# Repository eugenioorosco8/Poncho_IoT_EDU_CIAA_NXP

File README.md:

# Poncho_IoT_EDU_CIAA_NXP
El proyecto argentino CIAA, con alcance latinoamericano, lleva adelante el desarrollo y producción de sistemas embebidos, con fines educativos, industriales y científicos. El presente es un sistema embebido integral basado en la versión EDU-CIAA NXP, con fines educativos y de investigación aplicada. Se desarrolla el Hardware y el Software requeridos con el fin de proporcionar un circuito impreso de expansión de “Internet de las cosas” (IoT), capaz de brindar múltiples tecnologías como son: Wifi, Bluetooth, GSM, portabilidad SD, y RF. El desarrollo posee dos partes principales. La primera, basada en un microcontrolador ATMEL, consiste en la utilización de nodos provistos de sensores y módulos de comunicación. En la segunda parte, se diseña un nodo central de gran capacidad de procesamiento. La plataforma de desarrollo Nacional EDU-CIAA NXP, en conjunto con la placa de expansión IoT diseñada se emplea en la segunda etapa.

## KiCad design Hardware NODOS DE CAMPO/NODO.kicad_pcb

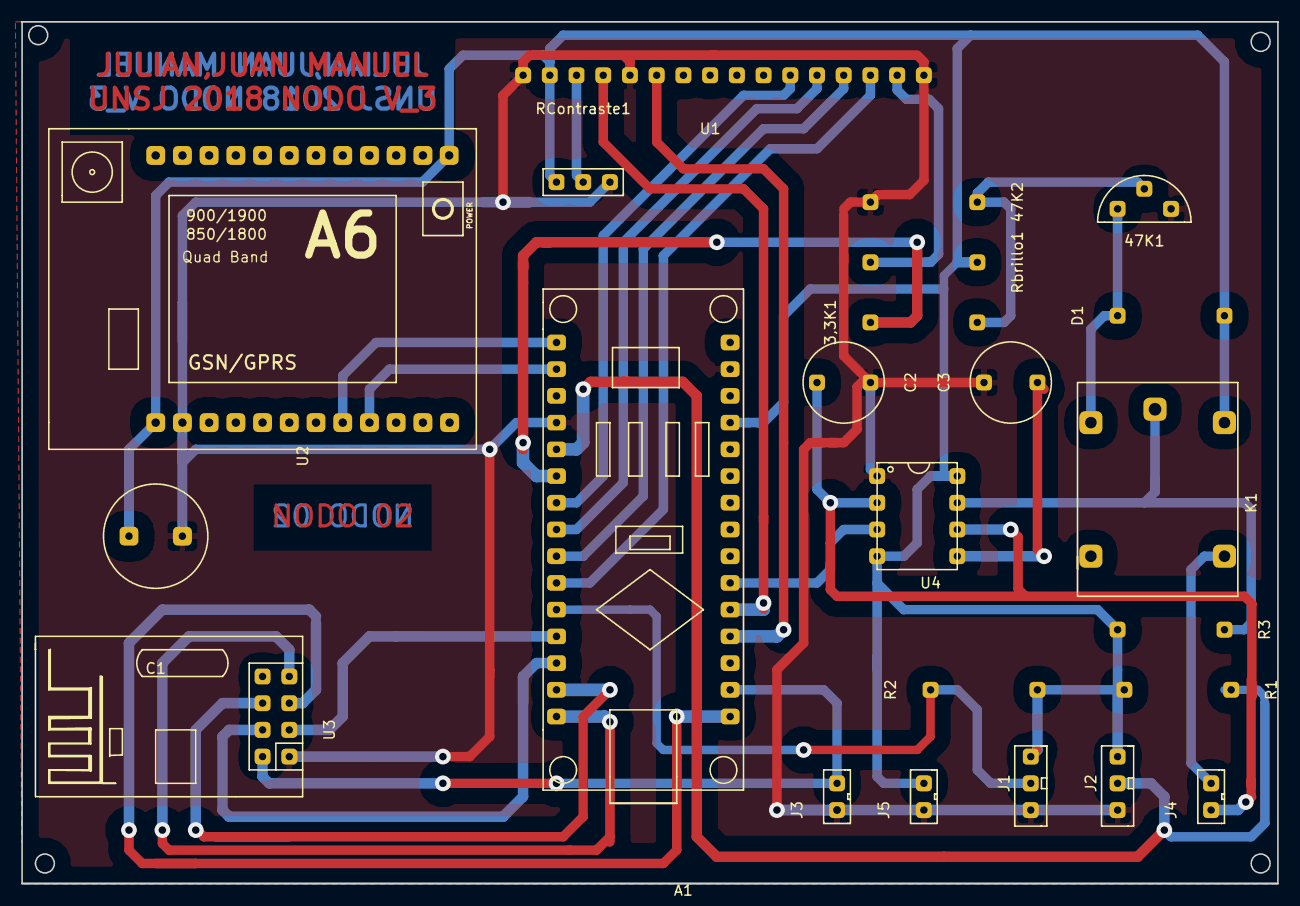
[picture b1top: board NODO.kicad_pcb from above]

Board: 2 copper layers, 119.4 x 81.9 mm, 23 parts (0 on the bottom side), 28 nets.

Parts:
3,3K1: R1; Resistencia
47K1: BC337; Transisitor_BC337
47K2: R2; Resistencia
A1: Arduino_Nano_v3.x; Arduino_nano
C1: CP; Capacitor_GSM
C2: 0.1; capacitor
C3: CP; capacitor
D1: 1N4007; Resistencia
J1: Temp Suelo; connectorx3
J2: DHT22; connectorx3
J3: C 3.3V; connectorx2
J4: Sensor_HumedadS; connectorx2
J5: C 5V; connectorx2
K1: G5Q-1; rele
R1, R2: 10K; Resistencia
R3: 1K; Resistencia
RContraste1: 10K; potenciometro_presicion
Rbrillo1: R; Resistencia
U1: lcd_1602
U2: A6_GSM
U3: NRF24L01_Breakout; modulo_rf
U4: LM555

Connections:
/3.3V: A1.17, J3.1, U3.2
/5V: A1.27, C1.1, D1.1, J1.1, J2.1, J5.1, K1.5, R1.1, R2.1, R3.1, RContraste1.3, Rbrillo1.2, U1.2, U2.1, U2.24, U4.4, U4.8
/13(SCK): A1.16, U3.5
/+_SHUM: K1.2, R3.2, U4.7
/D2: A1.5, J2.2, R1.2
/D3: 3,3K1.2, A1.6
/D4: A1.7, U1.11
/D5: A1.8, U1.12
/D6: A1.9, U1.13
/D7: A1.10, U1.14
/D8: A1.11, J1.2, R2.2
/D9: A1.12, U3.3
/D10: A1.13, U3.4
/D11(MOSI): A1.14, U3.6
/D12(MISO): A1.15, U3.7
/POT_M: RContraste1.2, U1.3
/RX: A1.1, U2.8
/R_LIGHT: Rbrillo1.1, U1.15
/S_HUM+: J4.1, K1.3
/S_HUM-: C2.1, J4.2, U4.2, U4.6
/S_Hum: A1.21, U4.3
/TX: A1.2, U2.9
GND: 47K1.3, 47K2.1, A1.4, A1.29, C1.2, C2.2, C3.2, J1.3, J2.3, J3.2, J5.2, RContraste1.1, U1.1, U1.5, U1.16, U2.2, U3.1, U4.1
unnamed: 3,3K1.1, 47K1.2, 47K2.2
unnamed: 47K1.1, D1.2, K1.1
unnamed: A1.19, U1.6
unnamed: A1.20, U1.4
unnamed: C3.1, U4.5

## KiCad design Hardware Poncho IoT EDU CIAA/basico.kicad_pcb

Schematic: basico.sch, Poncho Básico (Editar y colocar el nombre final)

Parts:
C1: CP; CP_Radial_D10.0mm_P5.00mm
RV1: R_POT_US
U1: NRF24L01_Breakout; nRF24L01_Breakout
U2: ESP8266_CIAA
U3: HC05
U4: SD_card_CIAA
U5: A6_GSM; A6_gsm
U6: lcd_1602
XA101: Conn_Poncho2P_2x_20x2; Conn_Poncho_SinBorde; Digikey# 952-1387-ND

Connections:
+3.3VP: U1.2, XA101.41 (+3.3V)
+3V3: U2.6, XA101.1 (+3.3V)
+5V: C1.1, RV1.1, U3.5, U4.2, U5.1, U6.1, U6.15, XA101.2 (+5V), XA101.42 (+5V)
/CE: U1.3, XA101.78 (GPIO7)
/CS: U4.6, XA101.74 (GPIO3)
/CSN: U1.4, XA101.69 (GPIO0)
/D4: U6.11, XA101.70 (lcd1)
/D5: U6.12, XA101.68 (lcd2)
/D6: U6.13, XA101.66 (lcd3)
/D7: U6.14, XA101.62 (lcd4)
/E: U6.6, XA101.63 (lcdEN)
/IRQ: U1.8, XA101.76 (GPIO5)
/MISO: U1.7, U4.3, XA101.58 (spiMISO)
/MOSI: U1.6, U4.4, XA101.61 (spiMOSI)
/PWR_A6: U5.24, XA101.80 (GPIO8)
/RS: U6.4, XA101.64 (lcdRS)
/SCK: U1.5, U4.5, XA101.60 (spiSCK)
/UART0_RX: U5.8, XA101.71 (GPIO2)
/UART0_TX: U5.9, XA101.72 (GPIO1)
/UART2_RX: U3.3, XA101.50 (ethCRS)
/UART2_TX: U3.2, XA101.49 (ethRXD0)
/UART3_RX: U2.5, XA101.23 (rs232RXD)
/UART3_TX: U2.4, XA101.25 (rs232TXD)
GND: C1.2, RV1.3, U1.1, U2.1, U3.4, U4.1, U5.2, U5.23, U6.2, U6.5, U6.7, U6.8, U6.9, U6.10, U6.16, XA101.4 (GND), XA101.40 (GND), XA101.43 (GND)
unnamed: RV1.2, U6.3

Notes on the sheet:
UART0
UART2
UART3
WI-FI
BLUETOOTH
GPRS
SD_CARD
SPI

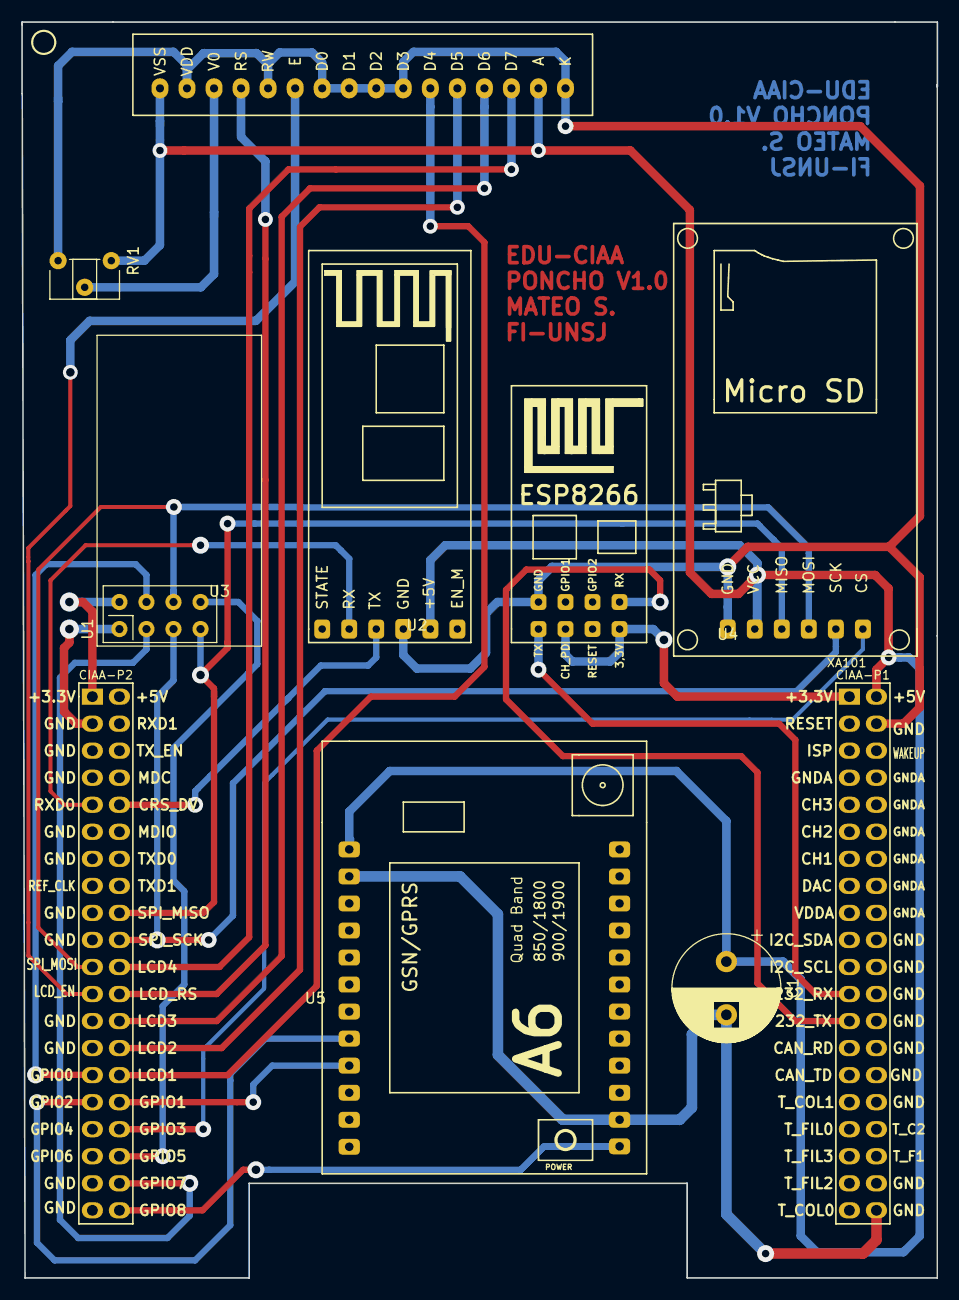
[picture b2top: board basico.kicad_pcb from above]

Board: 2 copper layers, 86.0 x 118.0 mm, 9 parts (0 on the bottom side), 25 nets.

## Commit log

2019-08-29 Rename Software NODO - Arduino/prueba_de_sensores_sase_n2/prueba_de_sensores_sase_n2.ino to Software NODO - Arduino/prueba_de_sensores_n2/prueba_de_sensores_n2.ino
